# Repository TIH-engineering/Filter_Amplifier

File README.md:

# Filter_Amplifier

## 🔌 Leiterplattenbeschreibung

Die Leiterplatte **Filter_Amplifier** dient zur praktischen Untersuchung von **aktiven Filtern und Operationsverstärkerschaltungen**. Sie wurde insbesondere für Laborübungen im Bereich Elektronik und Messtechnik entwickelt.

Die Schaltung besteht aus zwei hintereinander geschalteten Operationsverstärkerstufen mit einem **LM358**. Durch unterschiedliche Jumperstellungen können verschiedene Schaltungsvarianten realisiert und messtechnisch untersucht werden.

Folgende Betriebsarten sind vorgesehen:

- **nichtinvertierende Verstärkerschaltung**
- **Tiefpass 1. Ordnung**
- **Tiefpass 2. Ordnung**
- **Hochpass 1. Ordnung**
- **Hochpass 2. Ordnung**
- Untersuchung des Einflusses einer **kapazitiven Last** auf die Stabilität des Operationsverstärkers

Für die Filterschaltungen sind unterschiedliche Widerstands- und Kondensatorwerte vorgesehen. Dadurch können verschiedene Grenzfrequenzen eingestellt und deren Einfluss auf den Frequenzgang untersucht werden.

Ein- und Ausgang stehen über Koaxialanschlüsse zur Verfügung, sodass die Schaltung beispielsweise mit **Funktionsgenerator und Oszilloskop** vermessen werden kann. Die konfigurierbare Struktur ermöglicht insbesondere die experimentelle Untersuchung von **Verstärkung, Grenzfrequenz, Amplitudengang, Phasengang und Stabilität**.

> **Einsatzgebiet:** Laborübungen und Unterricht im Bereich Operationsverstärker, aktive Filter und Frequenzgangmessung

---

## 📥 Downloads

| Datei | Beschreibung |
|---|---|
| 📄 [Schaltplan (PDF)](../../releases/latest/download/schematic.pdf) | Schaltplan der Leiterplatte |
| 🖨️ [Leiterplatte (PDF)](../../releases/latest/download/pcb.pdf) | Leiterplattenansicht als PDF |
| 🔩 [Bohrplan (PDF)](../../releases/latest/download/drill.pdf) | Bohrdaten / Bohrplan |
| 📋 [Stückliste (Excel)](../../releases/latest/download/bom.xlsx) | Bill of Materials |
| 🌐 [Interactive BOM](../../releases/latest/download/ibom.html) | Interaktive Bestückungsansicht |
| 📦 [Fertigungsdaten](../../releases/latest/download/kicad.zip) | Gerber- und Bohrdaten |
| 🧊 [STEP-Modell](../../releases/latest/download/pcb.step) | 3D-Modell der Leiterplatte |

Die Dateien werden automatisch durch den Release-Workflow erzeugt.

---

## 🖥️ Leiterplatte

### Vorschau

| Oberseite | Unterseite |
|:---:|:---:|
|  |  |

### Oberseite

### Unterseite

---

## ℹ️ Projektinformationen

| Eigenschaft | Wert |
|---|---|
| **Projekt** | Filter_Amplifier |
| **Software** | KiCad 10 |
| **Repository** | TIH-engineering/Filter_Amplifier |
| **Autor** | TIH |
| **Lizenz** | CC BY-NC-SA 4.0 |

---

## 🗂️ Repository-Struktur

```text
.
├── .github/
│   └── workflows/       # GitHub Actions
├── .kibot/              # KiBot-Konfiguration
├── pcb/
│   ├── lib/             # Projektspezifische Bibliotheken
│   └── ...              # KiCad-Projektdateien
├── .gitignore
├── LICENSE
└── README.md

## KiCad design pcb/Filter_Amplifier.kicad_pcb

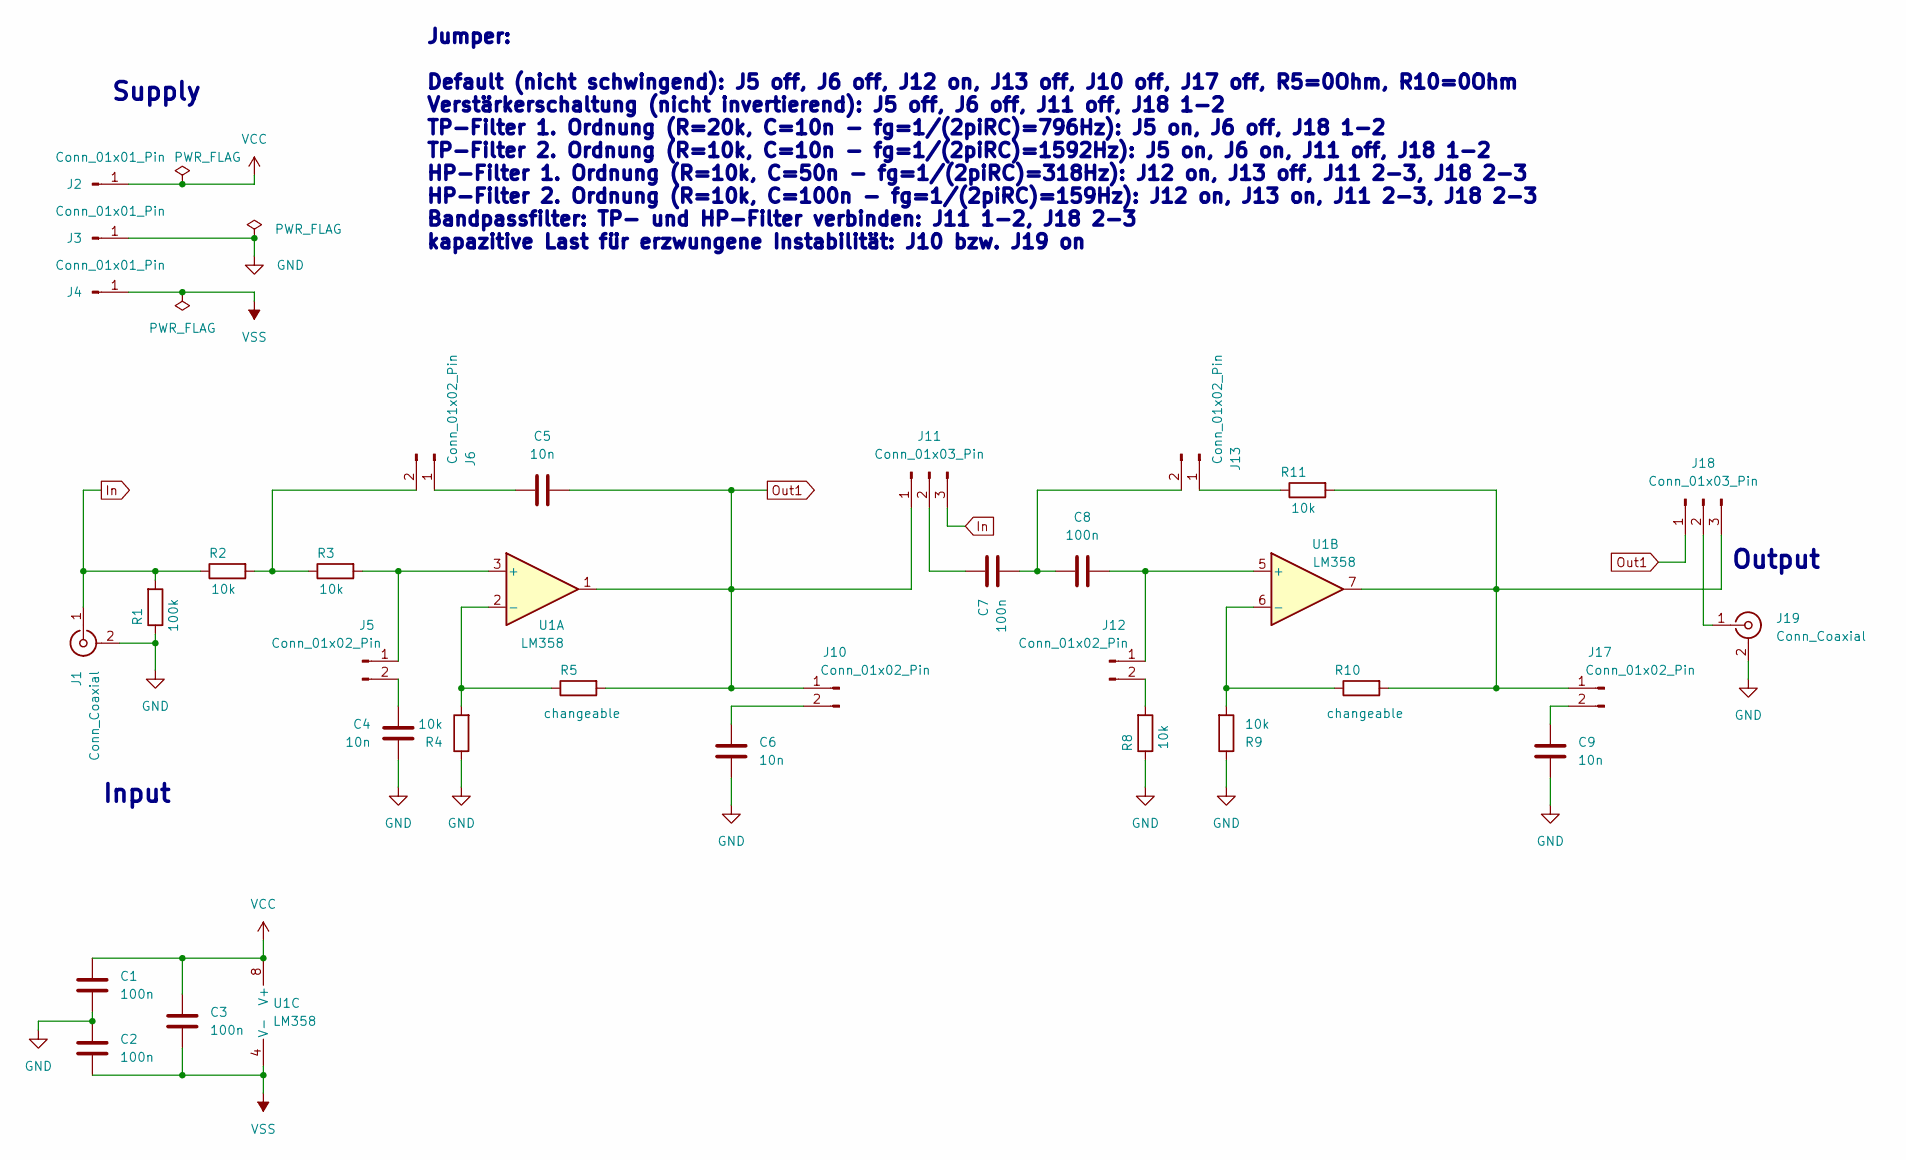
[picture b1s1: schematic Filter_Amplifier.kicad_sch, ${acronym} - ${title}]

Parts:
C1, C2, C3, C7, C8: 100n; C_1206_3216Metric_Pad1.33x1.80mm_HandSolder
C4, C5, C6, C9: 10n; C_1206_3216Metric_Pad1.33x1.80mm_HandSolder
J1, J19: Conn_Coaxial; BNC_TEConnectivity_1478204_Vertical
J2, J3, J4: Conn_01x01_Pin; PinHeader_1x01_P2.54mm_Vertical
J5, J6, J10, J12, J13, J17: Conn_01x02_Pin; PinHeader_1x02_P2.54mm_Vertical
J11, J18: Conn_01x03_Pin; PinHeader_1x03_P2.54mm_Vertical
R1: 100k; R_1206_3216Metric_Pad1.30x1.75mm_HandSolder
R2, R3, R4, R8, R9, R11: 10k; R_1206_3216Metric_Pad1.30x1.75mm_HandSolder
R5, R10: 10k; R_axial_SMD-Adapter_P10.16mm_1mm
U1: LM358; DIP-8_W7.62mm

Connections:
GND: C1.2, C2.1, C4.1, C6.2, C9.2, J1.2 (Ext), J3.1 (Pin_1_1), J19.2 (Ext), R1.1, R4.1, R8.1, R9.1
In: J1.1 (In), J11.3, R1.2, R2.1
unnamed: J5.1, R3.2, U1.3 (+)
unnamed: C4.2, J5.2
unnamed: C5.1, J6.1
unnamed: J6.2, R2.2, R3.1
unnamed: C6.1, J10.2
unnamed: C7.2, J11.2
unnamed: C8.1, J12.1, U1.5 (+)
unnamed: J12.2, R8.2
unnamed: J13.1, R11.1
unnamed: C7.1, C8.2, J13.2
unnamed: J17.1, J18.3, R10.2, R11.2, U1.7
unnamed: C9.1, J17.2
unnamed: J18.2, J19.1 (In)
unnamed: R4.2, R5.1, U1.2 (-)
unnamed: R9.2, R10.1, U1.6 (-)
Out1: C5.2, J10.1, J11.1, J18.1, R5.2, U1.1
VCC: C1.1, C3.1, J2.1 (Pin_1_1), U1.8 (V+)
VSS: C2.2, C3.2, J4.1 (Pin_1_1), U1.4 (V-)

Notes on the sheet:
Input
Supply
Output
Jumper: Default (nicht schwingend): J5 off, J6 off, J12 on, J13 off, J10 off, J17 off, R5=0Ohm, R10=0Ohm Verstärkerschaltung (nicht invertierend): J5 off, J6 off, J11 off, J18 1-2 TP-Filter 1. Ordnung (R=20k, C=10n - fg=1/(2piRC)=796Hz): J5 on, J6 off, J18 1-2 TP-Filter 2. Ordnung (R=10k, C=10n - f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

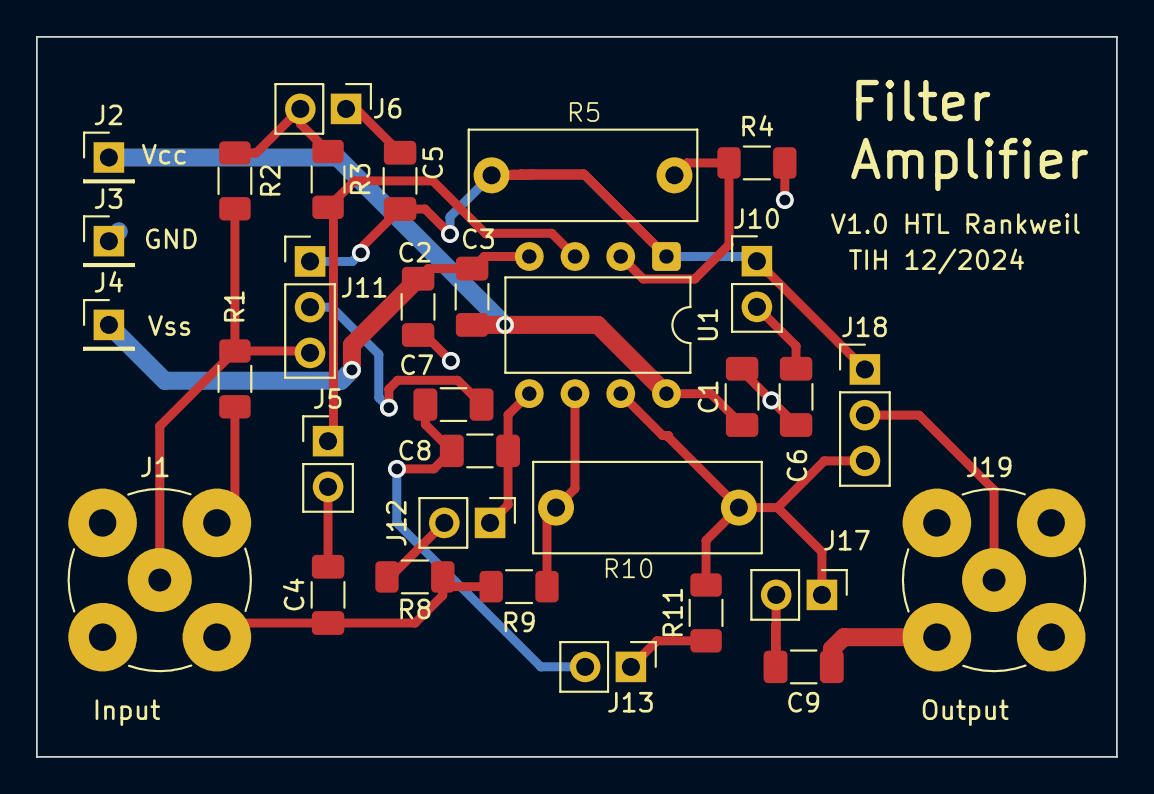
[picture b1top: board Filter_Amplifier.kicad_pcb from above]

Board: 2 copper layers, 60.0 x 40.0 mm, 32 parts (0 on the bottom side), 20 nets.

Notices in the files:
README.md:
License: CC-BY-NC-SA-4.0
